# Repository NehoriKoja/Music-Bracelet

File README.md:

# 🎵 Music Bracelet

<p align="center">
  **A wearable Bluetooth music controller.**
  <br>
  Control your music directly from your wrist without taking your phone out of your pocket.
</p>

---

## 📖 About the Project

The Music Bracelet is a custom-designed wearable Bluetooth media controller built around the ESP32-C3.

The goal is to create a compact bracelet that allows users to control music playback and volume through physical controls, without needing to interact with their phone.

The device combines custom PCB design, embedded electronics, battery management, and Bluetooth communication into a single wearable device.

**Submission Type:** Design Submission  
**Project Status:** Digital Design Completed – Hardware Development Pending 🚧

## 💡 Why I Made This

I wanted to create a small wearable device that makes controlling music more convenient.

Instead of constantly taking my phone out of my pocket to change songs or adjust the volume, I wanted to have these controls directly on my wrist.

I decided to design the entire electronic system myself, including the PCB, power management, and hardware layout, rather than relying on an existing development board or ready-made solution.

## ✨ Features

- **Bluetooth Connectivity:** Designed to connect to Android devices using the ESP32-C3's Bluetooth capabilities.
- **Media Controls:** Dedicated physical buttons for music playback.
- **Volume Control:** A rotary control for adjusting the volume.
- **Rechargeable Battery:** Integrated Li-Po charging circuit.
- **USB-C Charging:** Charging through a USB-C connector.
- **Compact PCB:** Custom-designed electronics intended to fit inside a wearable enclosure.
- **Standalone Operation:** Designed to work without a dedicated mobile application.

## 🖼️ Project Gallery

### 3D Assembly

*3D model of the bracelet enclosure, including the physical controls and charging port.*

**[🔗 View Full 3D Assembly on Onshape](https://cad.onshape.com/documents/3bd6b4cfeb2b41e224dd819f/w/d73a3a9d2469daf80b615cbf/e/bd991009cba7e1cd4ab621f9)**

### PCB Design

*3D render of the custom PCB designed in KiCad.*

### Schematic

*Electrical schematic showing the ESP32-C3 connections and battery charging circuit.*

## 🔌 Electronics

The project uses a custom PCB designed around the following components:

| Component | Purpose |
|---|---|
| ESP32-C3-MINI-1 | Main microcontroller and Bluetooth connectivity |
| MCP73871 | Li-Po battery charging and power management |
| AP2112K | Voltage regulation |
| USB-C Connector | Charging and USB connectivity |
| Rotary Encoder | Volume control |
| Push Buttons | Media controls |
| Li-Po Battery | Portable power source |
| Power Switch | Main power control |

## 📐 PCB Design

The PCB is designed using **KiCad**.

Some of the main design considerations include:

- Keeping the PCB as compact as possible.
- Making the physical controls accessible.
- Integrating the charging and power management circuits.
- Keeping the ESP32-C3 antenna clear of surrounding components.
- Designing the board to fit inside a wearable enclosure.

### PCB Source Files

The KiCad project files are included in this repository:

- [KiCad Project](./music%20bracelet%20schem.kicad_pro)
- [PCB Layout](./music%20bracelet%20schem.kicad_pcb)
- [Electrical Schematic](./music%20bracelet%20schem.kicad_sch)
- [PCB Project Settings](./music%20bracelet%20schem.kicad_prl)

### Manufacturing Files

The Gerber and drill files are packaged together for PCB manufacturing.

**[📥 Download Gerber Files (ZIP)](./gerbers.zip)**

## 🧾 Bill of Materials (BOM)

The Bill of Materials contains the electronic components used in the Music Bracelet project.

It includes component information, quantities, and manufacturing details.

**[📥 View Bill of Materials (CSV)](./BOM.csv)**

## 💻 Firmware

The firmware will run on the ESP32-C3 and handle:

- Bluetooth connection and communication.
- Media playback commands.
- Volume control.
- Reading physical button inputs.
- Battery and power management.

The firmware is currently under development.

**[💻 View Firmware Source Code](./main.cpp)**

## 🏗️ Mechanical Design

The bracelet enclosure was designed as a custom 3D model to house the electronics and provide access to the physical controls.

The mechanical design focuses on:

- A compact wearable form factor.
- Accessible physical buttons and volume control.
- A USB-C charging port.
- Proper space for the PCB and battery.

### Mechanical Files

- [Full 3D Assembly on Onshape](https://cad.onshape.com/documents/3bd6b4cfeb2b41e224dd819f/w/d73a3a9d2469daf80b615cbf/e/bd991009cba7e1cd4ab621f9)
- [Bracelet Case – STEP](./bracelet%20case.step)
- [Closed Case – STEP](./case%20closed.step)
- [PCB 3D Model – STEP](./music%20bracelet%20schem.step)

## 🛠️ Tools & Technologies

- **KiCad** – PCB design and schematic capture.
- **ESP32-C3** – Main microcontroller.
- **Embedded C/C++** – Firmware development.
- **Onshape** – Mechanical design and 3D modeling.
- **STEP** – 3D model exchange and manufacturing.

## 🚧 Development Roadmap

### Digital Design

The initial digital design includes the PCB, electrical schematic, component selection, BOM, and mechanical enclosure.

### Next Steps

1. Manufacture the custom PCB.
2. Assemble the electronic components.
3. Integrate the PCB and battery into the enclosure.
4. Develop and upload the firmware.
5. Implement Bluetooth media controls.
6. Test charging and battery management.
7. Test the complete system.
8. Finalize the bracelet assembly.

## 🎯 Future Plans

After completing the digital design, the next step is to manufacture the PCB and assemble the bracelet.

The final goal is to have a fully functional wearable device that can connect to a phone and control music reliably.

---

<p align="center">
  **Designed and developed by me.** 🎵
</p>

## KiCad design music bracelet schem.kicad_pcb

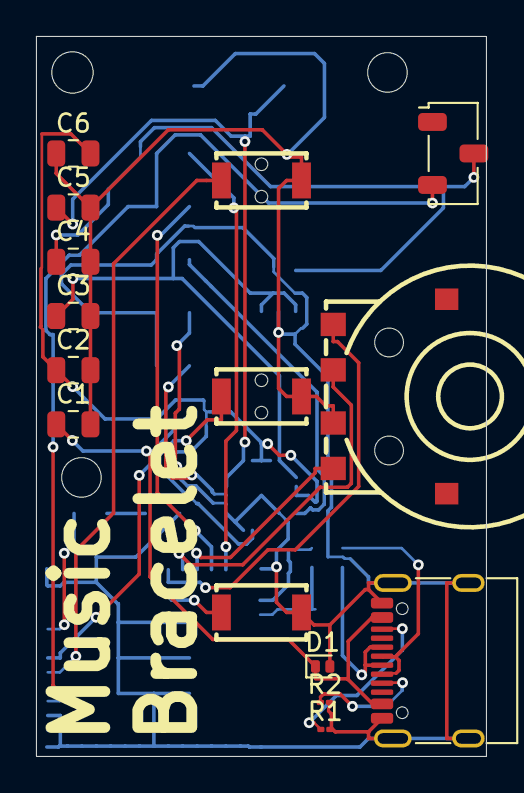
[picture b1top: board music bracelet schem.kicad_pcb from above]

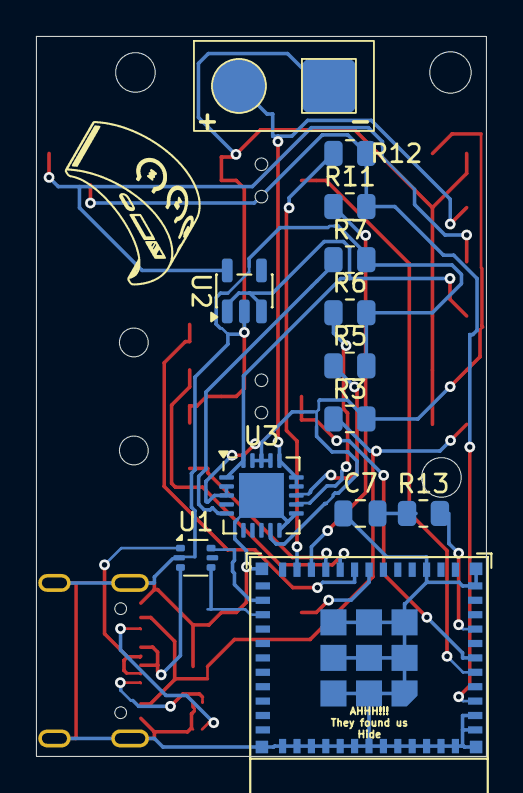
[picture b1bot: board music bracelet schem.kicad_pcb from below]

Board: 2 copper layers, 25.0 x 40.0 mm, 28 parts (13 on the bottom side), 26 nets.

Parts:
C1, C2, C3, C4, C5, C6: 4u7; C_0805_2012Metric
C7: 100nf; C_0805_2012Metric
D1: PESD5V0L1ULD; D_SOD-882D
R1, R2: 5k1; R_01005_0402Metric
R3: 0R; R_0805_2012Metric
R5: 6.8k; R_0805_2012Metric
R6, R7: 15k; R_0805_2012Metric
R11, R12, R13: 10k; R_0805_2012Metric
SW1: KH-SIQ-02FVS3
U1: USBLC6-2P6; SOT-666
U2: AP2112K-3.3; SOT-23-5
U3: MCP73871; QFN-20-1EP_4x4mm_P0.5mm_EP2.5x2.5mm
U4: ESP32-C3-MINI-1
battery_pads1: battery pads
button_1_skip1, button_2_pause/play1, button_3_previos1: SW_Push; KEY-SMD_L3.9-W3.0-LS5.0-EH
switch1: SW_Nidec_CAS-120A1; Nidec_Copal_CAS-120A
usb-c1: USB_C_Receptacle_USB2.0_16P; USB_C_Receptacle_G-Switch_GT-USB-7010ASV

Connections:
+3.3V: C4.1, U2.5 (VOUT), switch1.2 (B)
+5V: C2.1, C6.2, R3.2, U3.2 (VPCC), U3.3 (SEL), U3.9 (~TE), U3.17 (CE), U3.18 (IN), U3.19 (IN)
/D+: U1.3 (I/O2), usb-c1.A6 (D+), usb-c1.B6 (D+)
/D-: U1.1 (I/O1), usb-c1.A7 (D-), usb-c1.B7 (D-)
/PIN2: U4.5 (GPIO2/ADC1_CH2), button_1_skip1.1
/PIN3: U4.6 (GPIO3/ADC1_CH3), button_2_pause/play1.1
/PIN4: U4.18 (GPIO4/ADC1_CH4), button_3_previos1.1
/PIN5: SW1.A, U4.19 (GPIO5/ADC2_CH0)
/PIN6: SW1.S, U4.20 (GPIO6)
/PIN7: SW1.B, U4.21 (GPIO7)
B+: C5.1, U3.14 (V_{BAT}), U3.15 (V_{BAT}), U3.16 (V_{BAT_SENSE}), battery_pads1.1
B-: C1.2, C2.2, C3.2, C4.2, C5.2, C6.1, C7.1, D1.2 (A), R1.2, R2.2, R5.2, R6.2, R7.2, SW1.C, U1.2 (GND), U2.2 (GND), U3.10 (V_{SS}), U3.11 (V_{SS}), U3.21 (V_{SS}), U4.1 (GND), U4.2 (GND), U4.11 (GND), U4.14 (GND), U4.36 (GND), U4.37 (GND), U4.38 (GND), U4.39 (GND), U4.40 (GND), U4.41 (GND), U4.42 (GND), U4.43 (GND), U4.44 (GND), U4.45 (GND), U4.46 (GND), U4.47 (GND), U4.48 (GND), U4.49 (GND), U4.50 (GND), U4.51 (GND), U4.52 (GND), U4.53 (GND), battery_pads1.2, button_1_skip1.2, button_2_pause/play1.2, button_3_previos1.2, usb-c1.A1 (GND), usb-c1.A12 (GND), usb-c1.B1 (GND), usb-c1.B12 (GND), usb-c1.SH (SHIELD)
ESP_3.3V: R11.2, R12.2, U4.3 (3V3), switch1.3 (A)
unnamed: C7.2, R13.1
unnamed: R5.1, U3.13 (PROG1)
unnamed: R6.1, U3.12 (PROG3)
unnamed: R7.1, U3.5 (THERM)
unnamed: R13.2, U4.8 (EN/CHIP_PU)
unnamed: R11.1, U4.22 (GPIO8)
unnamed: R12.1, U4.23 (GPIO9)
unnamed: R2.1, usb-c1.A5 (CC1)
unnamed: R1.1, usb-c1.B5 (CC2)
SYS_VIN: C3.1, U2.1 (VIN), U2.3 (EN), U3.1 (OUT), U3.20 (OUT)
USB_D+: U1.4 (I/O2), U4.27 (GPIO19/USB_D+)
USB_D-: U1.6 (I/O1), U4.26 (GPIO18/USB_D-)
VBUS: C1.1, D1.1 (K), R3.1, usb-c1.A4 (VBUS), usb-c1.A9 (VBUS), usb-c1.B4 (VBUS), usb-c1.B9 (VBUS)

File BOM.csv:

"Reference","Qty","Value","DNP","Exclude from BOM","Exclude from Board","Exclude from Simulation","Exclude from Position Files","Footprint","Datasheet"
"battery_pads1","1","","","","","","${EXCLUDE_FROM_POS_FILES}","battery connection:battery pads",""
"button_1_skip1,button_2_pause/play1,button_3_previos1","3","SW_Push","","","","","${EXCLUDE_FROM_POS_FILES}","BX-TS-26-342TP:KEY-SMD_L3.9-W3.0-LS5.0-EH",""
"C1,C2,C3,C4,C5,C6","6","4u7","","","","","${EXCLUDE_FROM_POS_FILES}","Capacitor_SMD:C_0805_2012Metric",""
"C7","1","100nf","","","","","${EXCLUDE_FROM_POS_FILES}","Capacitor_SMD:C_0805_2012Metric",""
"D1","1","PESD5V0L1ULD","","","","","${EXCLUDE_FROM_POS_FILES}","Diode_SMD:D_SOD-882D","""https://assets.nexperia.com/documents/data-sheet/PESD5V0L1ULD.pdf"
"R1,R2","2","5k1","","","","","${EXCLUDE_FROM_POS_FILES}","Resistor_SMD:R_01005_0402Metric",""
"R3","1","0R","","","","","${EXCLUDE_FROM_POS_FILES}","Resistor_SMD:R_0805_2012Metric",""
"R5","1","6.8k","","","","","${EXCLUDE_FROM_POS_FILES}","Resistor_SMD:R_0805_2012Metric",""
"R6,R7","2","15k","","","","","${EXCLUDE_FROM_POS_FILES}","Resistor_SMD:R_0805_2012Metric",""
"R11,R12,R13","3","10k","","","","","${EXCLUDE_FROM_POS_FILES}","Resistor_SMD:R_0805_2012Metric",""
"SW1","1","KH-SIQ-02FVS3","","","","","${EXCLUDE_FROM_POS_FILES}","KH-SIQ-02FVS3:KH-SIQ-02FVS3",""
"switch1","1","SW_Nidec_CAS-120A1","","","","","${EXCLUDE_FROM_POS_FILES}","Button_Switch_SMD:Nidec_Copal_CAS-120A","https://www.nidec-components.com/e/catalog/switch/cas.pdf"
"U1","1","USBLC6-2P6","","","","","${EXCLUDE_FROM_POS_FILES}","Package_TO_SOT_SMD:SOT-666","https://www.st.com/resource/en/datasheet/usblc6-2.pdf"
"U2","1","AP2112K-3.3","","","","","${EXCLUDE_FROM_POS_FILES}","Package_TO_SOT_SMD:SOT-23-5","https://www.diodes.com/assets/Datasheets/AP2112.pdf"
"U3","1","MCP73871","","","","","${EXCLUDE_FROM_POS_FILES}","Package_DFN_QFN:QFN-20-1EP_4x4mm_P0.5mm_EP2.5x2.5mm","http://www.mouser.com/ds/2/268/22090a-52174.pdf"
"U4","1","ESP32-C3-MINI-1","","","","","${EXCLUDE_FROM_POS_FILES}","PCM_Espressif:ESP32-C3-MINI-1","https://www.espressif.com/sites/default/files/documentation/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"
"usb-c1","1","USB_C_Receptacle_USB2.0_16P","","","","","${EXCLUDE_FROM_POS_FILES}","Connector_USB:USB_C_Receptacle_G-Switch_GT-USB-7010ASV","https://www.usb.org/sites/default/files/documents/usb_type-c.zip"
